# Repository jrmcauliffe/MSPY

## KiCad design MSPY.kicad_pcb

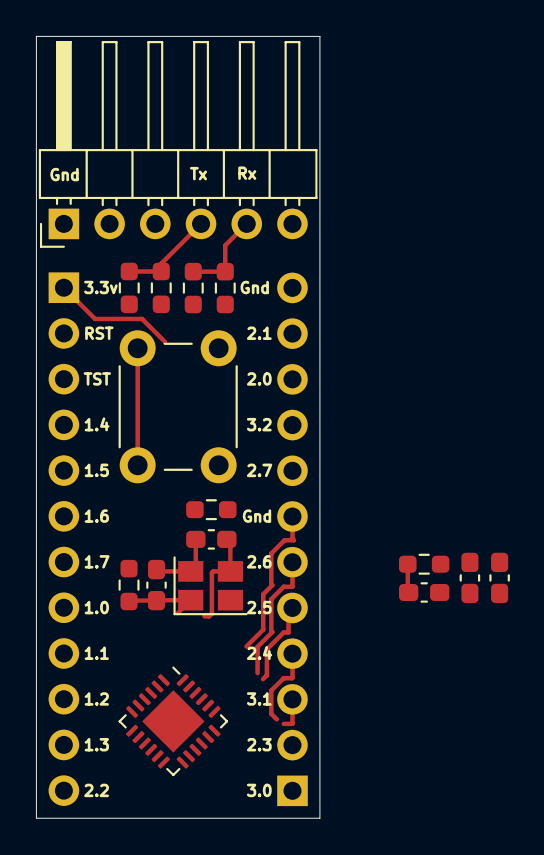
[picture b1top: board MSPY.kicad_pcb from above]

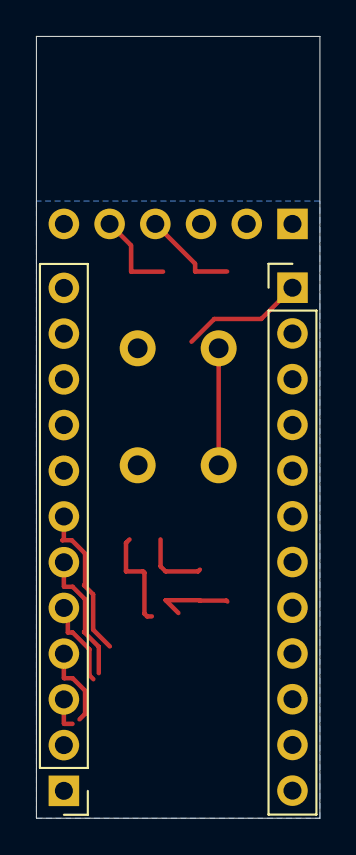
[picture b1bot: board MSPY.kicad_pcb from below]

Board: 2 copper layers, 15.7 x 43.4 mm, 18 parts (2 on the bottom side), 27 nets.

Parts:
C1: 10uF; C_0603_1608Metric_Pad1.08x0.95mm_HandSolder
C2: 100nF; C_0603_1608Metric_Pad1.08x0.95mm_HandSolder
C3: 1nF; C_0603_1608Metric_Pad1.08x0.95mm_HandSolder
C4: 33 pF; C_0603_1608Metric_Pad1.08x0.95mm_HandSolder
C5: 33 pf; C_0603_1608Metric_Pad1.08x0.95mm_HandSolder
J1: Conn_01x06; PinHeader_1x06_P2.54mm_Horizontal
J2, J3: Conn_01x12; PinHeader_1x12_P2.54mm_Vertical
R1, R2, R3, R4, R6, R7: 0; R_0603_1608Metric_Pad0.98x0.95mm_HandSolder
R5: 47k; R_0603_1608Metric_Pad0.98x0.95mm_HandSolder
SW1: SW_Push; SW_PUSH_6mm_H5mm
U1: MSP430FR2433RGE; VQFN-24-1EP_4x4mm_P0.5mm_EP2.45x2.45mm
Y1: Crystal_GND24; Crystal_SMD_SeikoEpson_TSX3225-4Pin_3.2x2.5mm

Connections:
P1: C3.1, J2.2, R5.2, SW1.1, U1.1 (RST/NMI/SBWTDIO)
P2: J2.3, U1.2 (TEST/SBWTCK)
P3: J2.4, R3.1, U1.3 (P1.4/UCA0TXD/UCA0SIMO/TA1.2/TCK/A4/VREF+)
P4: J2.5, R1.1, U1.4 (P1.5/UCA0RXD/UCA0SOMI/TA1.1/TMS/A5)
P5: J2.6, U1.5 (P1.6/UCA0CLK/TA1CLK/TDI/TCLK/A6)
P6: J2.7, U1.6 (P1.7/UCA0STE/SMCLK/TDO/A7)
P7: J2.8, U1.7 (P1.0/UCB0STE/TA0CLK/A0/Veref+)
P8: J2.9, U1.8 (P1.1/UCB0CLK/TA0.1/A1)
P9: J2.10, U1.9 (P1.2/UCB0SIMO/UCB0SDA/TA0.2/A2/Veref)
P10: J2.11, U1.10 (P1.3/UCB0SOMI/UCB0SCL/MCLK/A3)
P11: J2.12, U1.11 (P2.2/ACLK)
P12: J3.1, U1.12 (P3.0)
P13: J3.2, U1.13 (P2.3)
P14: J3.3, U1.14 (P3.1/UCA1STE)
P15: J3.4, U1.15 (P2.4/UCA1CLK)
P16: J3.5, R2.1, U1.16 (P2.5/UCA1RXD/UCA1SOMI)
P17: J3.6, R4.1, U1.17 (P2.6/UCA1TXD/UCA1SIMO)
P19: J3.8, U1.19 (P2.7)
P20: J3.9, U1.20 (P3.2)
P21: J3.10, R7.1
P22: J3.11, R6.1
RX: J1.4, R1.2, R2.2
TX: J1.5, R3.2, R4.2
VCC: C1.1, C2.1, J2.1, R5.1, U1.24 (DVCC)
VSS: C1.2, C2.2, C3.2, C4.2, C5.2, J1.1, J3.7, J3.12, SW1.2, U1.18 (DVSS), U1.23 (DVSS), U1.25 (VSS), Y1.2, Y1.4
XIN: C4.1, R6.2, U1.22 (P2.1/XIN), Y1.1
XOUT: C5.1, R7.2, U1.21 (P2.0/XOUT), Y1.3

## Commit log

2020-05-24 v1.0
2023-07-31 Update to kicad 6 and add UART selector
2023-12-31 Update to kicad 7
